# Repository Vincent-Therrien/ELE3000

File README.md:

# ELE3000
Projet de troisième année à Polytechnique Montréal par
Vincent Therrien (vincent.therrien@polymtl.ca)

La documentation est générée avec le programme Sphinx, utilisé pour générer
la documentation officielle de Python. Les fichiers source sont écrits avec
la syntaxe Restructured Text (rst) et la documentation peut être compilée sous
plusieurs formes.

## Documentation HTML

Ouvrez le fichier "html/index.html" pour consulter la documentation sous format
HTML.

## Documentation PDF

Ouvrez le fichier "ele3000_latex.pdf" pour consulter la documentation en PDF.

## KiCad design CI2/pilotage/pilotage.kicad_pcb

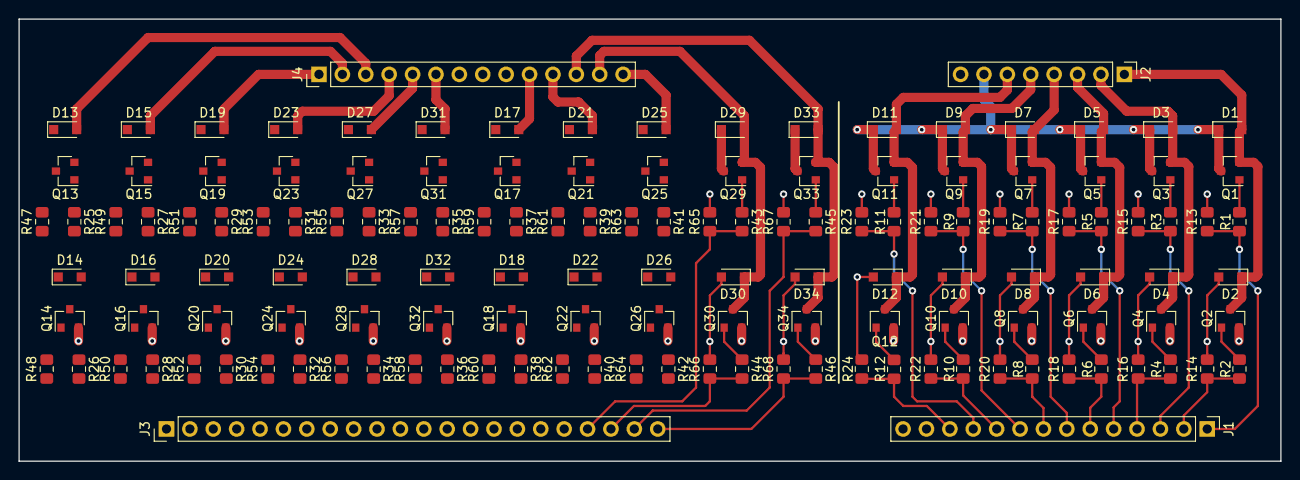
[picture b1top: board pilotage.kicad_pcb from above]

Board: 2 copper layers, 137.0 x 48.0 mm, 140 parts (0 on the bottom side), 88 nets.

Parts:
D1, D2, D3, D4, D5, D6, D7, D8, D9, D10, D11, D12, D13, D14, D15, D16, D17, D18, D19, D20, D21, D22, D23, D24, D25, D26, D27, D28, D29, D30, D31, D32, D33, D34: 1N4148; D_SOD-323_HandSoldering
J1, J4: Conn_01x14_Male; PinHeader_1x14_P2.54mm_Vertical
J2: Conn_01x08_Male; PinHeader_1x08_P2.54mm_Vertical
J3: Conn_01x22_Male; PinHeader_1x22_P2.54mm_Vertical
Q1, Q2, Q3, Q4, Q5, Q6, Q7, Q8, Q9, Q10, Q11, Q12, Q13, Q14, Q15, Q16, Q17, Q18, Q19, Q20, Q21, Q22, Q23, Q24, Q25, Q26, Q27, Q28, Q29, Q30, Q31, Q32, Q33, Q34: Q_NMOS_GSD; SOT-23
R1, R2, R3, R4, R5, R6, R7, R8, R9, R10, R11, R12, R25, R26, R27, R28, R29, R30, R31, R32, R33, R34, R35, R36, R37, R38, R39, R40, R41, R42, R43, R44, R45, R46: 51; R_0805_2012Metric_Pad1.15x1.40mm_HandSolder
R13, R14, R15, R16, R17, R18, R19, R20, R21, R22, R23, R24, R47, R48, R49, R50, R51, R52, R53, R54, R55, R56, R57, R58, R59, R60, R61, R62, R63, R64, R65, R66, R67, R68: 20k; R_0805_2012Metric_Pad1.15x1.40mm_HandSolder

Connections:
+6V: D1.1, D3.1, D5.1, D7.1, D9.1, D11.1, J2.7, Q1.3, Q3.3, Q5.3, Q7.3, Q9.3, Q11.3
+7.5V: D13.1, D15.1, D17.1, D19.1, D21.1, D23.1, D25.1, D27.1, D29.1, D31.1, D33.1, J4.7, Q13.3, Q15.3, Q17.3, Q19.3, Q21.3, Q23.3, Q25.3, Q27.3, Q29.3, Q31.3, Q33.3
GND: D2.2, D4.2, D6.2, D8.2, D10.2, D12.2, D14.2, D16.2, D18.2, D20.2, D22.2, D24.2, D26.2, D28.2, D30.2, D32.2, D34.2, J1.14, J2.8, J4.8, Q2.2, Q4.2, Q6.2, Q8.2, Q10.2, Q12.2, Q14.2, Q16.2, Q18.2, Q20.2, Q22.2, Q24.2, Q26.2, Q28.2, Q30.2, Q32.2, Q34.2, R13.2, R14.2, R15.2, R16.2, R17.2, R18.2, R19.2, R20.2, R21.2, R22.2, R23.2, R24.2, R47.2, R48.2, R49.2, R50.2, R51.2, R52.2, R53.2, R54.2, R55.2, R56.2, R57.2, R58.2, R59.2, R60.2, R61.2, R62.2, R63.2, R64.2, R65.2, R66.2, R67.2, R68.2
unnamed: J1.1, R1.2, R13.1
unnamed: J1.2, R2.2, R14.1
unnamed: J1.3, R3.2, R15.1
unnamed: J1.4, R4.2, R16.1
unnamed: J1.5, R5.2, R17.1
unnamed: J1.6, R6.2, R18.1
unnamed: J1.7, R7.2, R19.1
unnamed: J1.8, R8.2, R20.1
unnamed: J1.9, R9.2, R21.1
unnamed: J1.10, R10.2, R22.1
unnamed: J1.11, R11.2, R23.1
unnamed: J1.12, R12.2, R24.1
unnamed: J3.1, R25.2, R47.1
unnamed: J3.2, R26.2, R48.1
unnamed: J3.3, R27.2, R49.1
unnamed: J3.4, R28.2, R50.1
unnamed: J3.5, R29.2, R51.1
unnamed: J3.6, R30.2, R52.1
unnamed: J3.7, R31.2, R53.1
unnamed: J3.8, R32.2, R54.1
unnamed: J3.9, R33.2, R55.1
unnamed: J3.10, R34.2, R56.1
unnamed: J3.11, R35.2, R57.1
unnamed: J3.12, R36.2, R58.1
unnamed: J3.13, R37.2, R59.1
unnamed: J3.14, R38.2, R60.1
unnamed: J3.15, R39.2, R61.1
unnamed: J3.16, R40.2, R62.1
unnamed: J3.17, R41.2, R63.1
unnamed: J3.18, R42.2, R64.1
unnamed: J3.19, R43.2, R65.1
unnamed: J3.20, R44.2, R66.1
unnamed: J3.21, R45.2, R67.1
unnamed: J3.22, R46.2, R68.1
c1b: Q4.1, R4.1
c1h: Q3.1, R3.1
c2b: Q6.1, R6.1
c2h: Q5.1, R5.1
c3b: Q8.1, R8.1
c3h: Q7.1, R7.1
c4b: Q10.1, R10.1
c4h: Q9.1, R9.1
c5b: Q12.1, R12.1
c5h: Q11.1, R11.1
cb: Q2.1, R2.1
ch: Q1.1, R1.1
d1b: Q18.1, R38.1
d1h: Q17.1, R37.1
d2b: Q22.1, R40.1
d2h: Q21.1, R39.1
d3b: Q26.1, R42.1
d3h: Q25.1, R41.1
d4b: Q30.1, R44.1
d4h: Q29.1, R43.1
d5b: Q34.1, R46.1
d5h: Q33.1, R45.1
g1b: Q16.1, R28.1
g1h: Q15.1, R27.1
g2b: Q20.1, R30.1
g2h: Q19.1, R29.1
g3b: Q24.1, R32.1
g3h: Q23.1, R31.1
g4b: Q28.1, R34.1
g4h: Q27.1, R33.1
g5b: Q32.1, R36.1
g5h: Q31.1, R35.1
moteur_c_1_b: D3.2, D4.1, J2.2, Q3.2, Q4.3
moteur_c_2_b: D5.2, D6.1, J2.3, Q5.2, Q6.3
moteur_c_3_b: D7.2, D8.1, J2.4, Q7.2, Q8.3
moteur_c_4_b: D9.2, D10.1, J2.5, Q9.2, Q10.3
moteur_c_5_b: D11.2, D12.1, J2.6, Q11.2, Q12.3
moteur_c_a: D1.2, D2.1, J2.1, Q1.2, Q2.3
moteur_d_1_b: D17.2, D18.1, J4.10, Q17.2, Q18.3
moteur_d_2_b: D21.2, D22.1, J4.11, Q21.2, Q22.3
moteur_d_3_b: D25.2, D26.1, J4.14, Q25.2, Q26.3
moteur_d_4_b: D29.2, D30.1, J4.13, Q29.2, Q30.3
moteur_d_5_b: D33.2, D34.1, J4.12, Q33.2, Q34.3
moteur_g_1_b: D15.2, D16.1, J4.2, Q15.2, Q16.3
moteur_g_2_b: D19.2, D20.1, J4.1, Q19.2, Q20.3
moteur_g_3_b: D23.2, D24.1, J4.4, Q23.2, Q24.3
moteur_g_4_b: D27.2, D28.1, J4.5, Q27.2, Q28.3
moteur_g_5_b: D31.2, D32.1, J4.6, Q31.2, Q32.3
moteur_s_a: D13.2, D14.1, J4.3, Q13.2, Q14.3
sb: Q14.1, R25.1
sh: Q13.1, R26.1

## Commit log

2021-01-30 Ajout de la documentation
2021-01-30 Faute de frappe
2021-01-30 Signature
2021-02-28 Mise à jour de la réalisation physique de l'appareil
2021-02-28 Ajout d'images comme preuve
2021-03-13 Ajout de l'application
2021-03-14 Ajout du PCB
